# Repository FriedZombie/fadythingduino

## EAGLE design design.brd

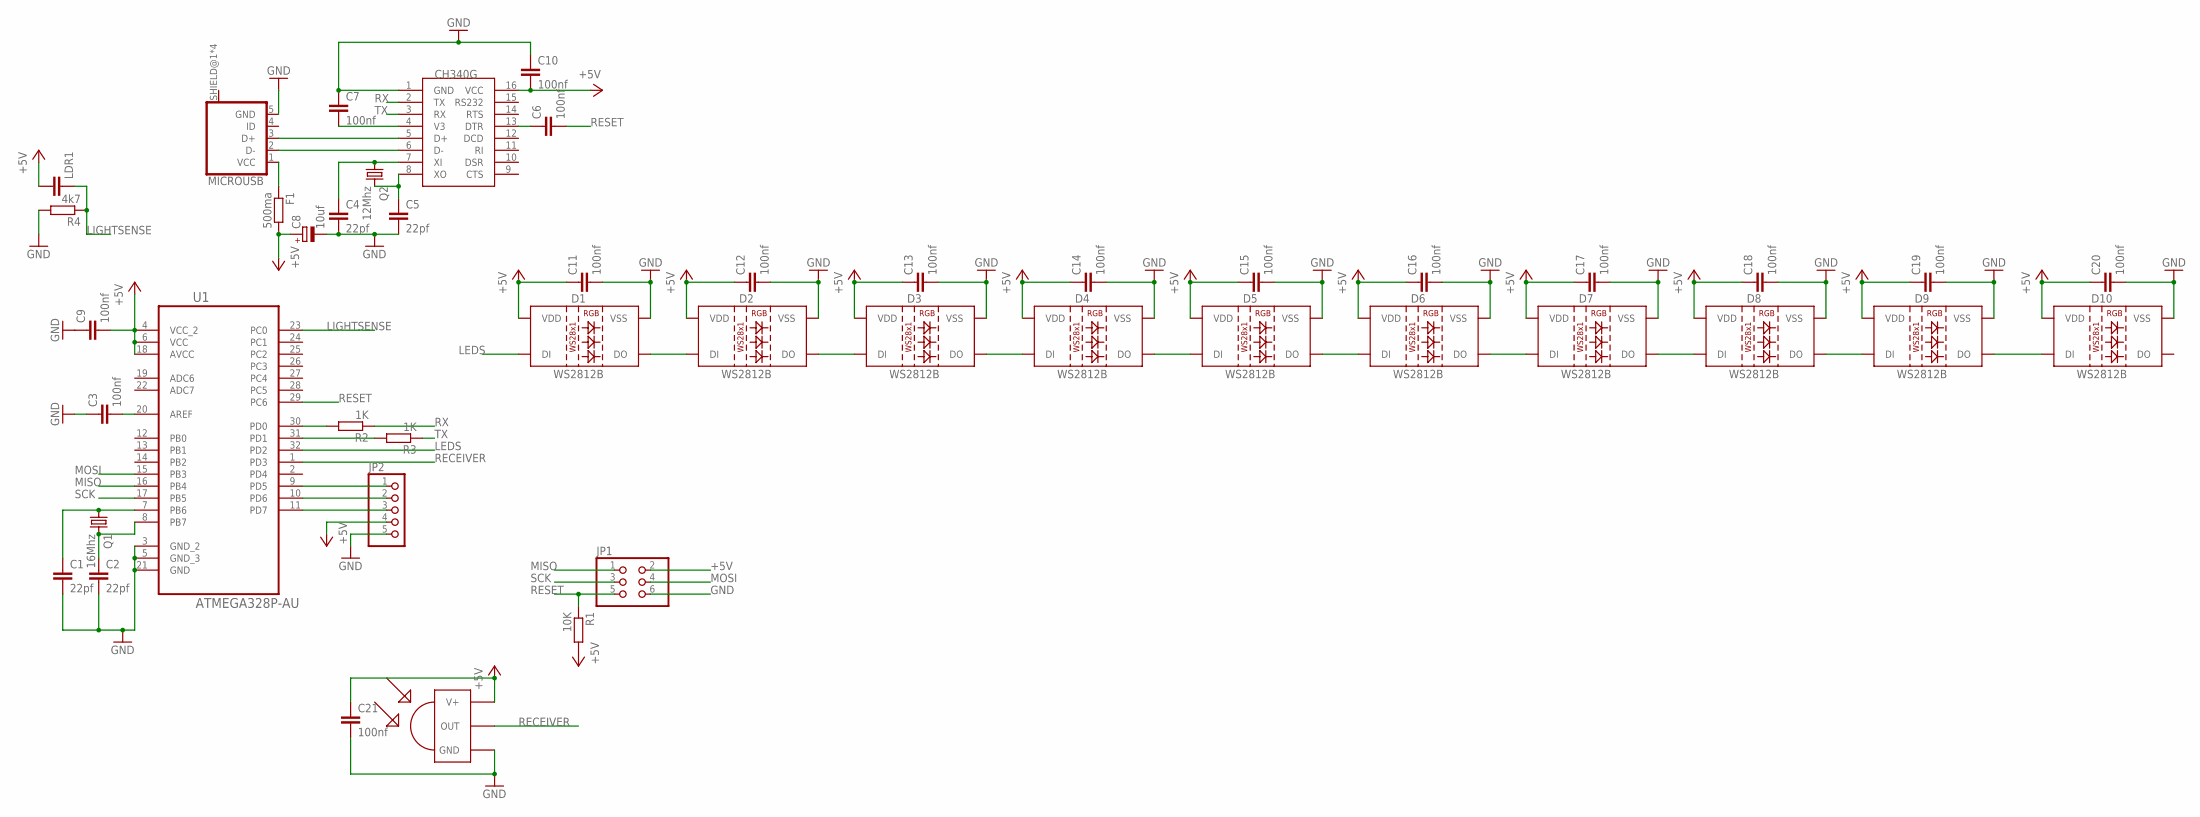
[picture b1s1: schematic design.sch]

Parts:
C1, C2, C4, C5: 22pf; C0603
C3, C6, C7, C9, C10, C11, C12, C13, C14, C15, C16, C17, C18, C19, C20, C21: 100nf; C0603
C8: 10uf; PANASONIC_C
D1, D2, D3, D4, D5, D6, D7, D8, D9, D10: WS2812B
F1: 500ma; R1206
JP1: PINHD-2X3; 2X03
JP2: PINHD-1X5; 1X05
LDR1: C-EU025-030X050; C025-030X050
MICROUSB: MICROUSB; MICROSUSB
Q1: 16Mhz; HC49/S
Q2: 12Mhz; HC49/S
R1: 10K; R0603
R2, R3: 1K; R0603
R4: 4k7; R0603
U1: ATMEGA328P-AU; QFP80P900X900X120-32N
U2: CH340G; SOIC16
U$3: TSOP1838; TSOP18XX

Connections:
+5V: C8.+, C9.2, C10.2, C11.1, C12.1, C13.1, C14.1, C15.1, C16.1, C17.1, C18.1, C19.1, C20.1, C21.1, D1.1 (VDD), D2.1 (VDD), D3.1 (VDD), D4.1 (VDD), D5.1 (VDD), D6.1 (VDD), D7.1 (VDD), D8.1 (VDD), D9.1 (VDD), D10.1 (VDD), F1.2, JP1.2, JP2.4, LDR1.2, R1.2, U1.4 (VCC_2), U1.6 (VCC), U1.18 (AVCC), U2.16 (VCC), U$3.VCC (V+)
D+: MICROUSB.3 (D+), U2.5 (D+)
D-: MICROUSB.2 (D-), U2.6 (D-)
GND: C1.2, C2.2, C3.1, C4.2, C5.2, C7.1, C8.-, C9.1, C10.1, C11.2, C12.2, C13.2, C14.2, C15.2, C16.2, C17.2, C18.2, C19.2, C20.2, C21.2, D1.3 (VSS), D2.3 (VSS), D3.3 (VSS), D4.3 (VSS), D5.3 (VSS), D6.3 (VSS), D7.3 (VSS), D8.3 (VSS), D9.3 (VSS), D10.3 (VSS), JP1.6, JP2.5, MICROUSB.5 (GND), R4.2, U1.3 (GND_2), U1.5 (GND_3), U1.21 (GND), U2.1 (GND), U$3.GND
LEDS: D1.4 (DI), U1.32 (PD2)
LIGHTSENSE: LDR1.1, R4.1, U1.23 (PC0)
MISO: JP1.1, U1.16 (PB4)
MOSI: JP1.4, U1.15 (PB3)
unnamed: C2.1, Q1.2, U1.8 (PB7)
unnamed: C1.1, Q1.1, U1.7 (PB6)
unnamed: C3.2, U1.20 (AREF)
unnamed: R2.2, U1.30 (PD0)
unnamed: JP2.1, U1.9 (PD5)
unnamed: R3.2, U1.31 (PD1)
unnamed: JP2.2, U1.10 (PD6)
unnamed: C4.1, Q2.1, U2.7 (XI)
unnamed: C5.1, Q2.2, U2.8 (XO)
unnamed: C6.1, U2.13 (DTR)
unnamed: C7.2, U2.4 (V3)
unnamed: F1.1, MICROUSB.1 (VCC)
unnamed: JP2.3, U1.11 (PD7)
unnamed: D3.2 (DO), D4.4 (DI)
unnamed: D4.2 (DO), D5.4 (DI)
unnamed: D5.2 (DO), D6.4 (DI)
unnamed: D6.2 (DO), D7.4 (DI)
unnamed: D7.2 (DO), D8.4 (DI)
unnamed: D8.2 (DO), D9.4 (DI)
unnamed: D1.2 (DO), D2.4 (DI)
unnamed: D2.2 (DO), D3.4 (DI)
unnamed: D9.2 (DO), D10.4 (DI)
RECEIVER: U1.1 (PD3), U$3.OUT
RESET: C6.2, JP1.5, R1.1, U1.29 (PC6)
RX: R2.1, U2.2 (TX)
SCK: JP1.3, U1.17 (PB5)
SHIELD: MICROUSB.SHIELD@1 (SHIELD), MICROUSB.SHIELD@2 (SHIELD), MICROUSB.SHIELD@3 (SHIELD), MICROUSB.SHIELD@4 (SHIELD)
TX: R3.1, U2.3 (RX)

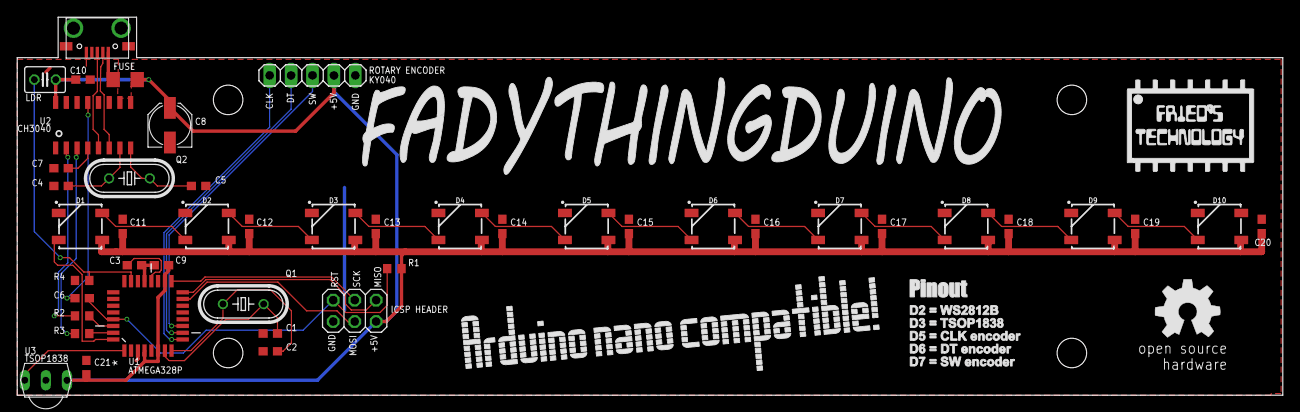
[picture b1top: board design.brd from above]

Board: 2 copper layers, 150.0 x 44.8 mm, 46 parts (0 on the bottom side), 36 nets.

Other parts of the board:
U$1: OSHW_8MM

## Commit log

2018-09-03 Added final result images for v0.2
2018-09-03 update readme with an image
2018-09-17 added open hardware logo and fixed an ugly trace
2019-01-07 Minor board updates
2019-01-07 removed zip from repo
2019-01-07 Updated board rendered images

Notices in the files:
parts and their libraries:
SparkFun-LED: Licensing: Creative Commons ShareAlike 4.0 International - https://creativecommons.org/licenses/by-sa/4.0
